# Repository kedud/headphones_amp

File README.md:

# Headphone amp

This module is an headphone amp (with a gain of 20dB) associated with a blend setting that allow user to listen to both Cue & Mix outputs, the blend potentiometer sets the proportion of each signal sent to the headphones output.

The BoM for this schematics can be found [here](https://octopart.com/bom-tool/wFRvv2qY)

A Mouser cart is also available [here](https://www.mouser.com/ProjectManager/ProjectDetail.aspx?AccessID=5afd9f8ce4)

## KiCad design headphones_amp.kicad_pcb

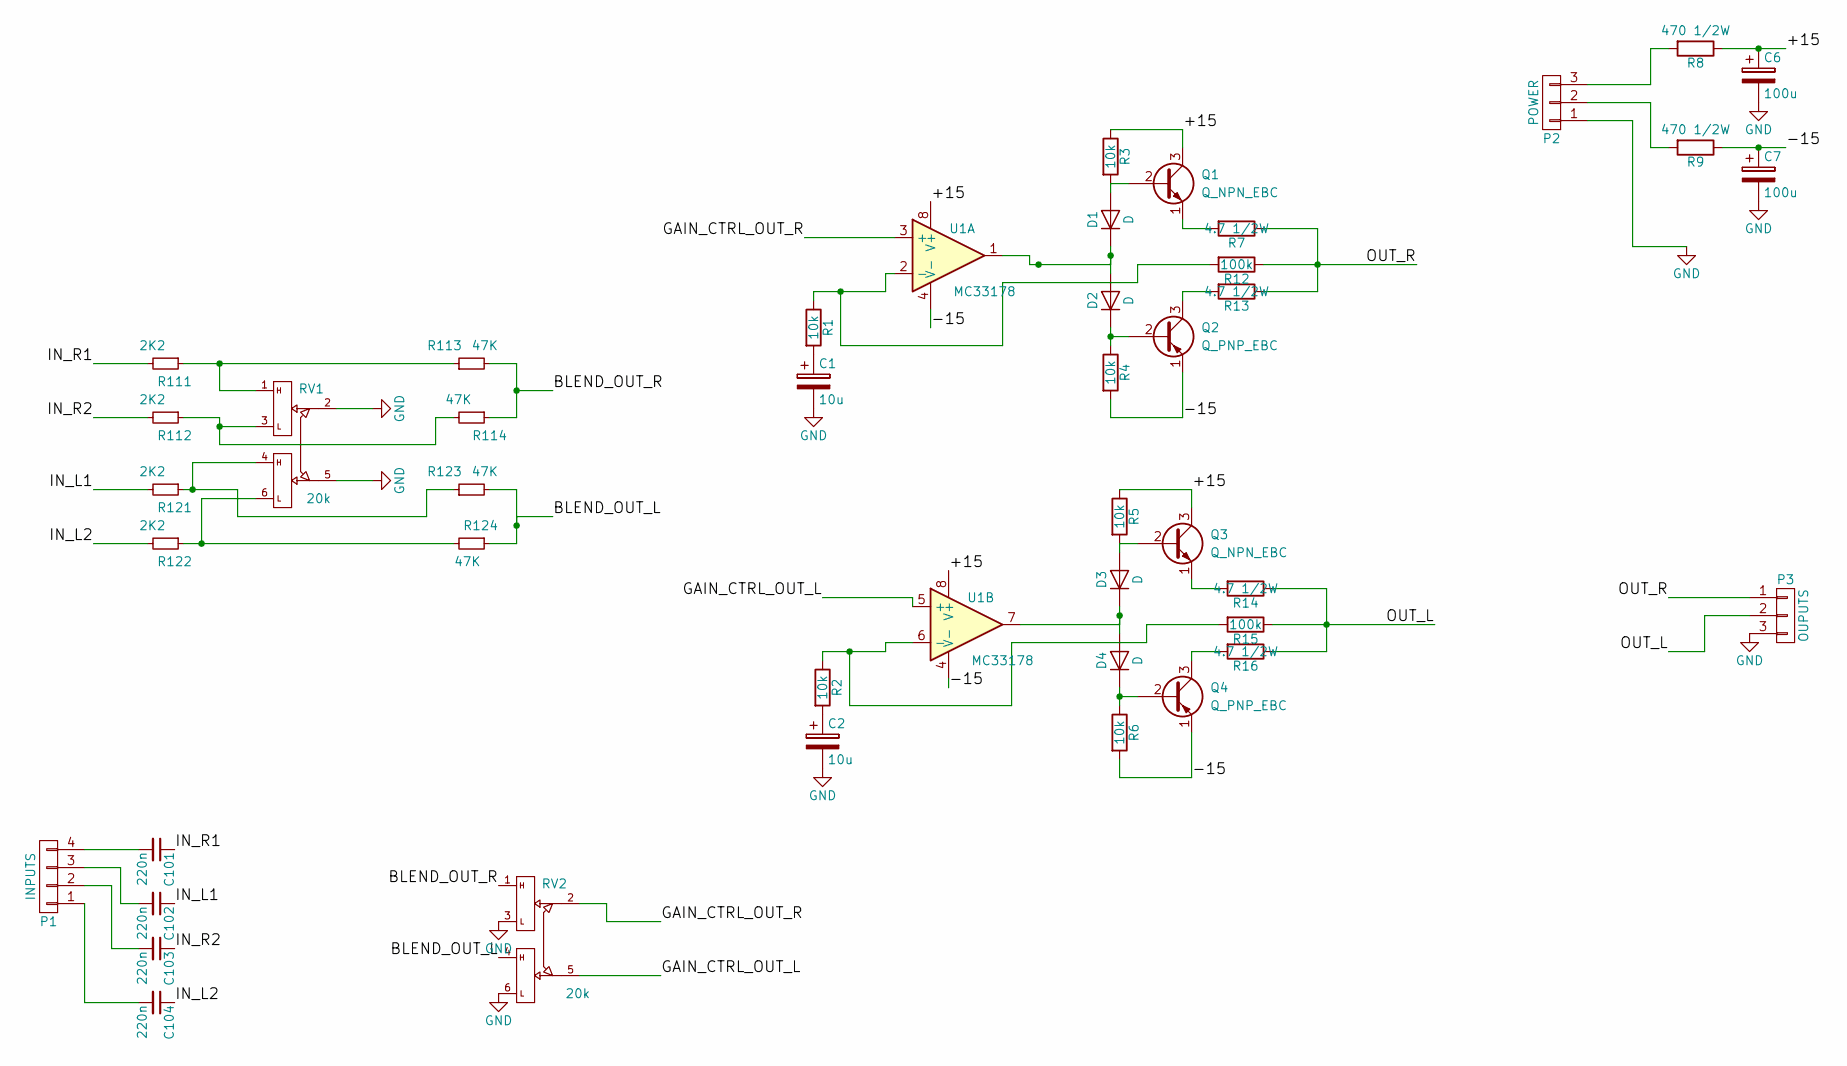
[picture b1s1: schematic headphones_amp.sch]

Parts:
C1, C2: 10u; CP_5x11mm; Mfg_Part_No USR1V100MDD1TE
C6, C7: 100u; CP_6.3x11mm; Mfg_Part_No ULD1E101MED1TD
C101, C102, C103, C104: 220n; C_Rect_L7.0mm_W3.5mm_P5.00mm; Mfg_Part_No R82EC3220Z370J
D1, D2, D3, D4: D; D_DO-35_SOD27_P7.62mm_Horizontal; Mfg_Part_No 1N4148
P1: INPUTS; Pin_Header_Angled_1x04_Pitch2.54mm; Mfg_Part_No 0
P2: POWER; Pin_Header_Angled_1x03_Pitch2.54mm
P3: OUPUTS; Pin_Header_Angled_1x03_Pitch2.54mm; Mfg_Part_No 0
Q1, Q3: Q_NPN_EBC; TO-18-3; Mfg_Part_No 2N2222
Q2, Q4: Q_PNP_EBC; TO-18-3; Mfg_Part_No 2N2907A
R1, R2, R3, R4, R5, R6: 10k; R_Axial_DIN0204_L3.6mm_D1.6mm_P5.08mm_Horizontal
R7, R13, R14, R16: 4.7 1/2W; R_Axial_DIN0204_L3.6mm_D1.6mm_P5.08mm_Horizontal
R8, R9: 470 1/2W; Resistor_Horizontal_RM7mm
R12, R15: 100k; R_Axial_DIN0204_L3.6mm_D1.6mm_P5.08mm_Horizontal
R111, R112, R121, R122: 2K2; R_Axial_DIN0204_L3.6mm_D1.6mm_P5.08mm_Horizontal
R113, R114, R123, R124: 47K; R_Axial_DIN0204_L3.6mm_D1.6mm_P5.08mm_Horizontal
RV1: 20k; Potentiometer_ALPS_RK097; Mfg_Part_No RK0971210Z2M
RV2: 20k; Potentiometer_ALPS_RK097; Mfg_Part_No RK09712200HA
U1: MC33178; DIP-8_W7.62mm_LongPads

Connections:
/+15: C6.1, Q1.3 (C), Q3.3 (C), R3.1, R5.1, R8.1, U1.8 (V+)
/-15: C7.1, Q2.1 (E), Q4.1 (E), R4.2, R6.2, R9.1, U1.4 (V-)
/BLEND_OUT_L: R123.2, R124.1, RV2.4
/BLEND_OUT_R: R113.2, R114.1, RV2.1
/GAIN_CTRL_OUT_L: RV2.5, U1.5 (+)
/GAIN_CTRL_OUT_R: RV2.2, U1.3 (+)
/IN_L1: C102.1, R121.2
/IN_L2: C104.1, R122.2
/IN_R1: C101.1, R111.2
/IN_R2: C103.1, R112.2
/OUT_L: P3.2, R14.1, R15.1, R16.1
/OUT_R: P3.1, R7.1, R12.1, R13.1
GND: C1.2, C2.2, C6.2, C7.2, P2.1, P3.3, RV1.2, RV1.5, RV2.3, RV2.6
unnamed: C1.1, R1.2
unnamed: C2.1, R2.2
unnamed: C101.2, P1.4
unnamed: C102.2, P1.3
unnamed: C103.2, P1.2
unnamed: C104.2, P1.1
unnamed: D1.1 (K), D2.2 (A), U1.1
unnamed: D1.2 (A), Q1.2 (B), R3.2
unnamed: D2.1 (K), Q2.2 (B), R4.1
unnamed: D3.1 (K), D4.2 (A), U1.7
unnamed: D3.2 (A), Q3.2 (B), R5.2
unnamed: D4.1 (K), Q4.2 (B), R6.1
unnamed: P2.2, R9.2
unnamed: P2.3, R8.2
unnamed: Q1.1 (E), R7.2
unnamed: Q2.3 (C), R13.2
unnamed: Q3.1 (E), R14.2
unnamed: Q4.3 (C), R16.2
unnamed: R1.1, R12.2, U1.2 (-)
unnamed: R2.1, R15.2, U1.6 (-)
unnamed: R111.1, R113.1, RV1.1
unnamed: R112.1, R114.2, RV1.3
unnamed: R121.1, R123.1, RV1.4
unnamed: R122.1, R124.2, RV1.6

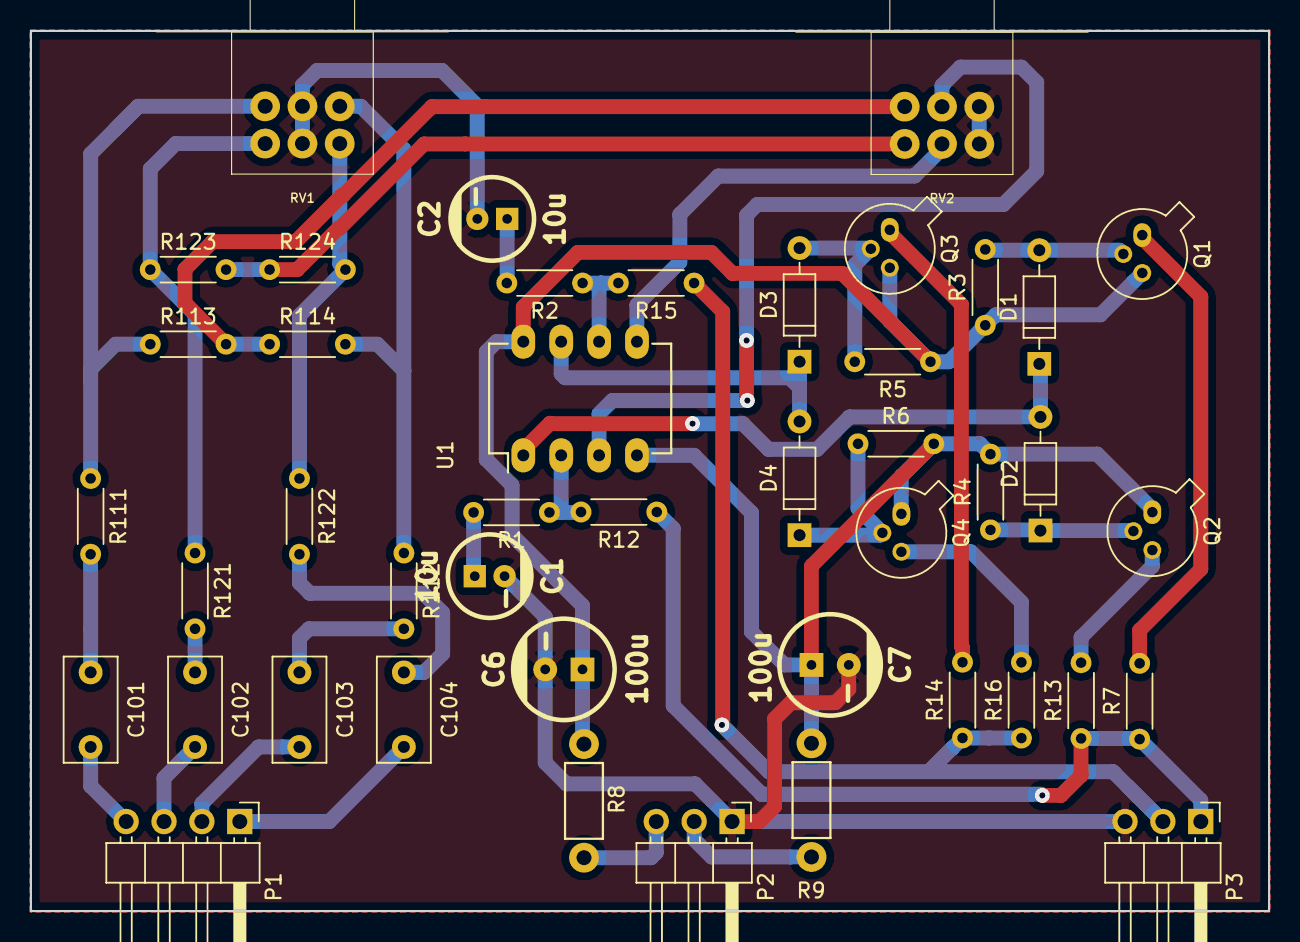
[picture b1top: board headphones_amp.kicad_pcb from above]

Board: 2 copper layers, 83.0 x 59.0 mm, 44 parts (0 on the bottom side), 37 nets.

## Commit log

2017-11-17 Updated components references
2017-11-17 Add missing references
2017-11-17 Add README.md
2017-11-17 Fix BoM links
2017-12-25 Updating .gitignore to ignore 3D files
